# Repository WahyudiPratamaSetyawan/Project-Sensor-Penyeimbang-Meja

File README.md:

# Project-Sensor-Penyeimbang-Meja
Project Sensor Penyeimbang Meja menggunakan sensor Sharp IR untuk mendeteksi kemiringan pada kedua sisi meja. Data kemiringan ditampilkan pada LCD 16x2, dan buzzer berbunyi saat meja terdeteksi miring.

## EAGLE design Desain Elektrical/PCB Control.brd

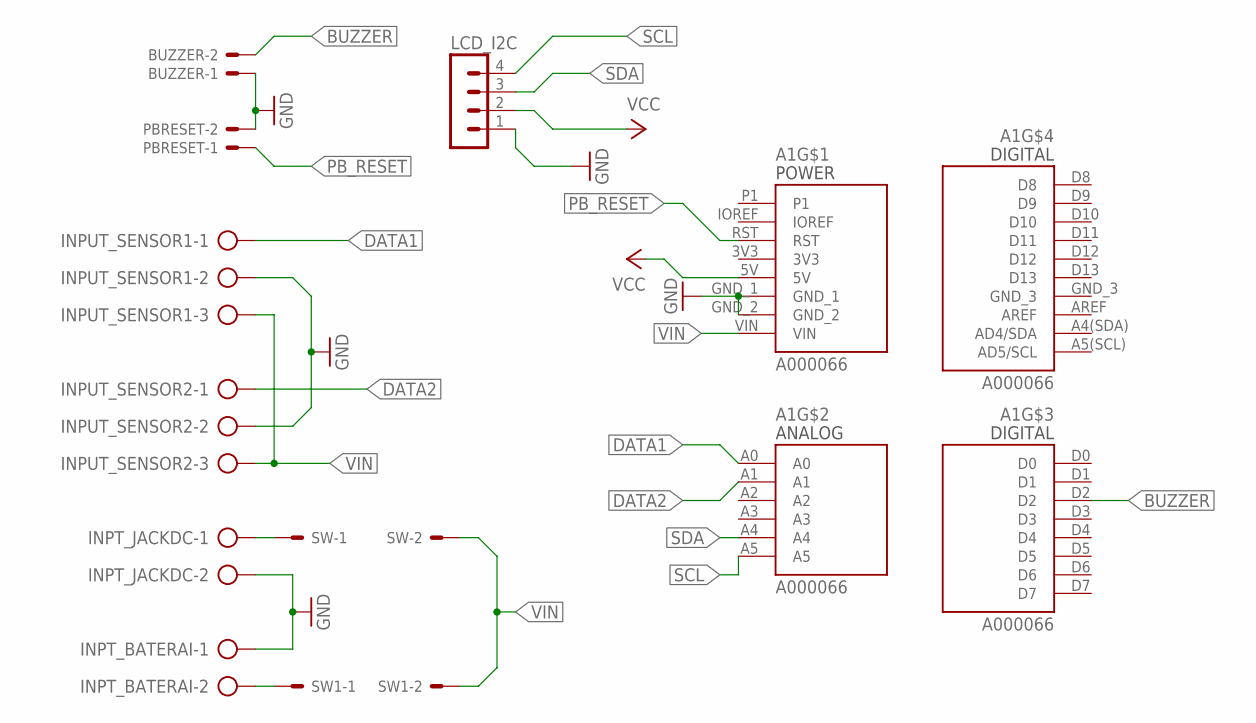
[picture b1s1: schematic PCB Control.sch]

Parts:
A1: A000066; ARDUINO_A000066
BUZZER: 22-23-2021
INPT_BATERAI: AK500/2
INPT_JACKDC: AK500/2
INPUT_SENSOR1, INPUT_SENSOR2: AK500/3
LCD_I2C: MA04-1
PBRESET: 22-23-2021
SW, SW1: 22-23-2021

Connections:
3V3: A1.3V3
BUZZER: A1.D2, BUZZER.2
DATA1: A1.A0, INPUT_SENSOR1.1
DATA2: A1.A1, INPUT_SENSOR2.1
GND: A1.GND_1, A1.GND_2, BUZZER.1, INPT_BATERAI.1, INPT_JACKDC.2, INPUT_SENSOR1.2, INPUT_SENSOR2.2, LCD_I2C.1, PBRESET.2
GND_3: A1.GND_3
unnamed: INPT_JACKDC.1, SW.1
unnamed: INPT_BATERAI.2, SW1.1
PB_RESET: A1.RST, PBRESET.1
SCL: A1.A5, LCD_I2C.4
SDA: A1.A4, LCD_I2C.3
VCC: A1.5V, LCD_I2C.2
VIN: A1.VIN, INPUT_SENSOR1.3, INPUT_SENSOR2.3, SW.2, SW1.2

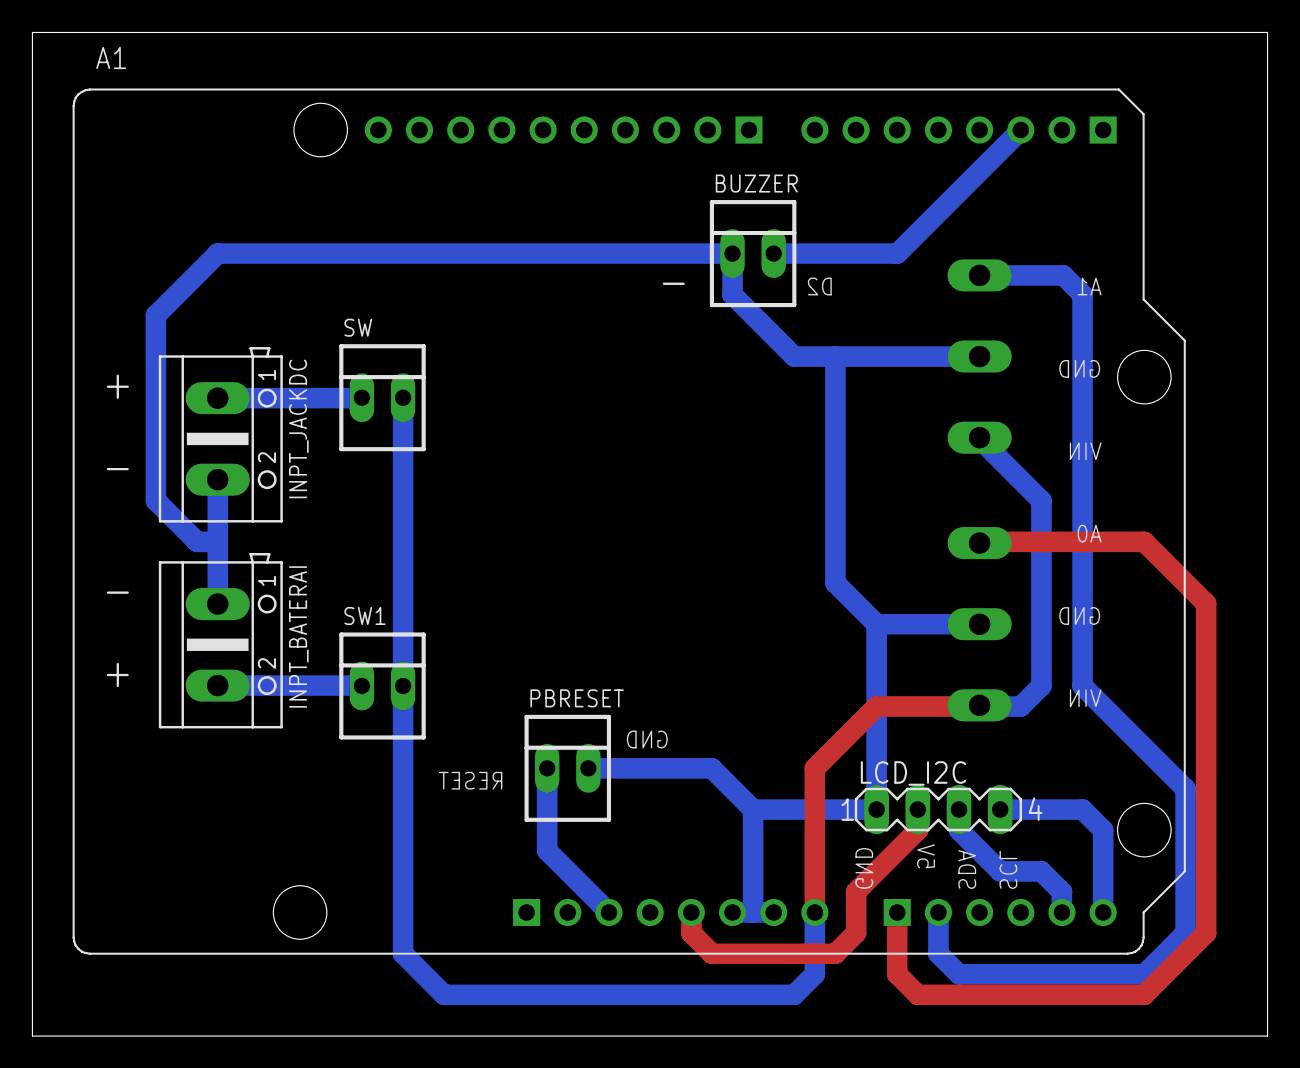
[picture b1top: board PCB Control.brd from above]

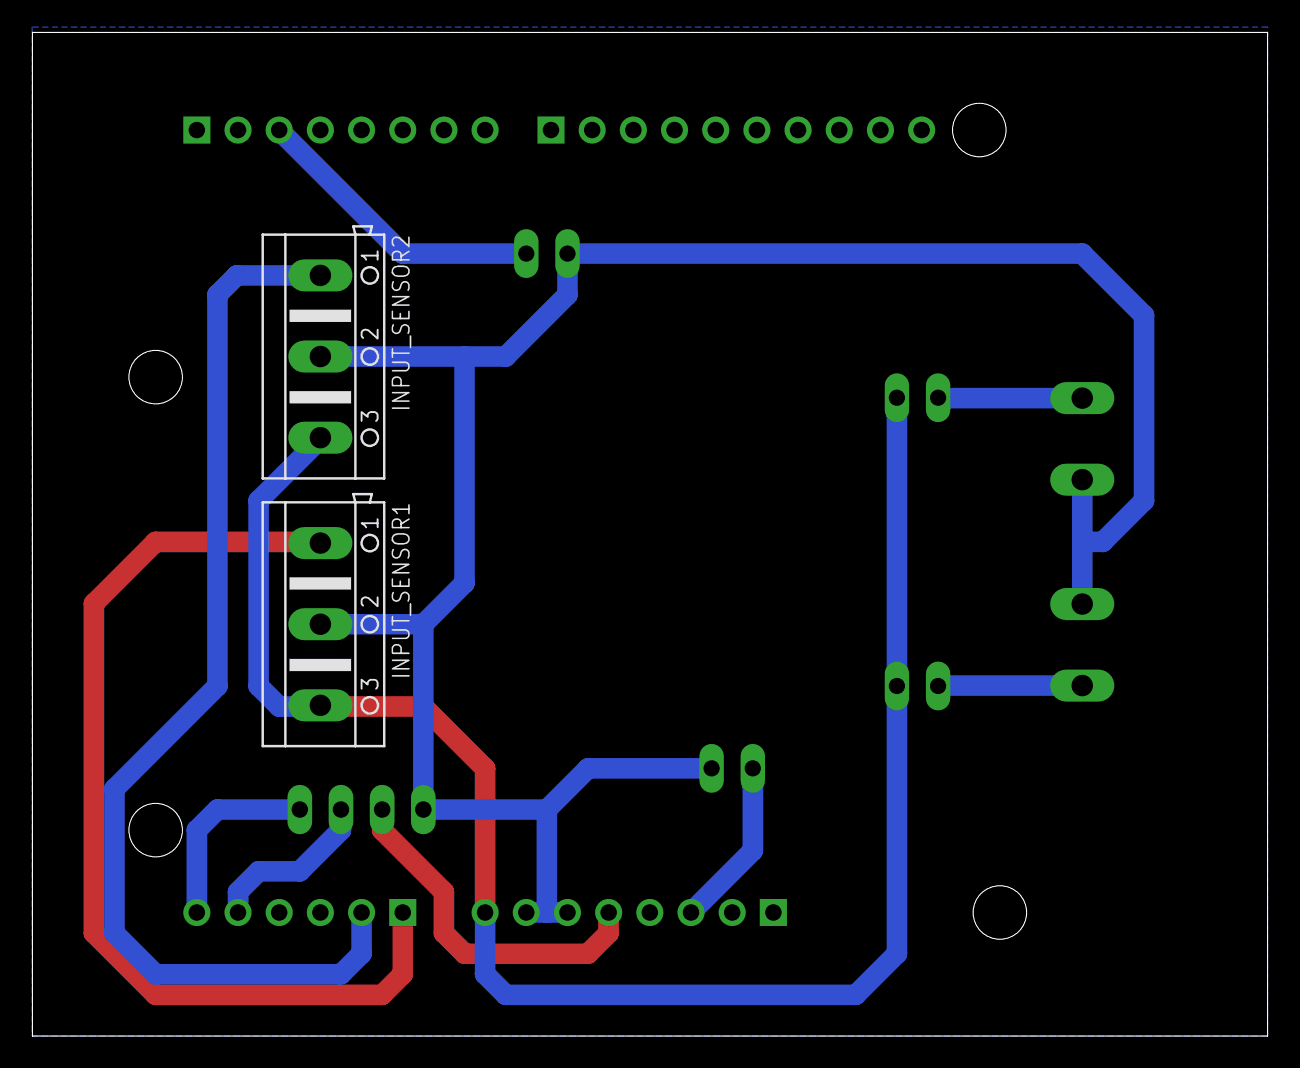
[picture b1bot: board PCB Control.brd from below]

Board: 2 copper layers, 76.2 x 61.9 mm, 10 parts (2 on the bottom side), 11 nets.

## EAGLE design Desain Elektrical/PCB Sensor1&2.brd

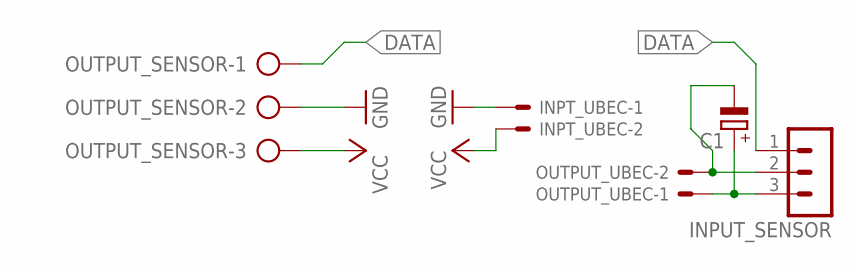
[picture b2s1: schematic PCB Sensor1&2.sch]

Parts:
C1: CPOL-EUE2-5; E2-5
INPT_UBEC: 22-23-2021
INPUT_SENSOR: MA03-1
OUTPUT_SENSOR: AK500/3
OUTPUT_UBEC: 22-23-2021

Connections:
DATA: INPUT_SENSOR.1, OUTPUT_SENSOR.1
GND: INPT_UBEC.1, OUTPUT_SENSOR.2
unnamed: C1.-, INPUT_SENSOR.2, OUTPUT_UBEC.2
unnamed: C1.+, INPUT_SENSOR.3, OUTPUT_UBEC.1
VCC: INPT_UBEC.2, OUTPUT_SENSOR.3

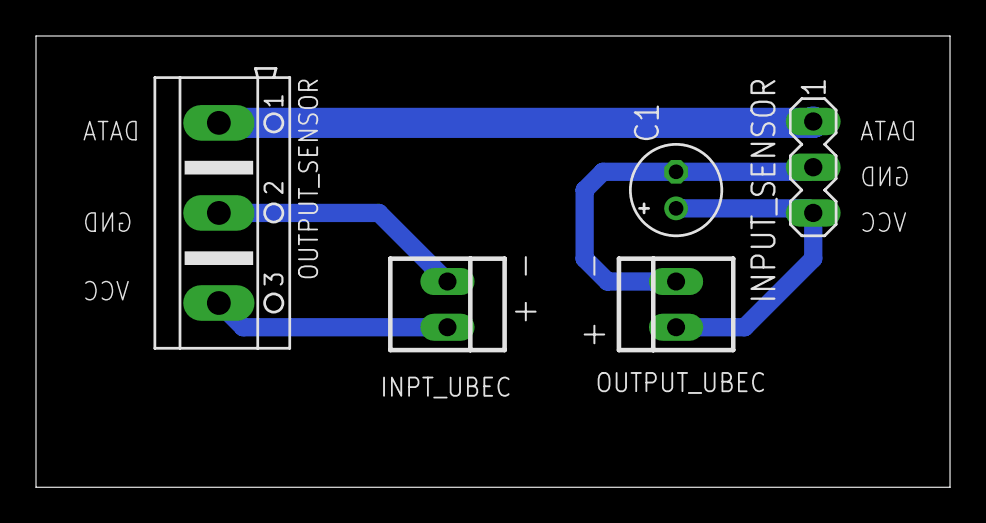
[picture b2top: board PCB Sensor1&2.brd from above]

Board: 2 copper layers, 50.8 x 25.1 mm, 5 parts (0 on the bottom side), 5 nets.

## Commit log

2025-05-29 Create Deskripsi
2025-06-01 Create tess
2025-06-01 Create tes
2025-06-01 Update and rename tes to Intruksi
